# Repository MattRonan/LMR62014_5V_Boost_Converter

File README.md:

# LMR62014_5V_Boost_Converter

A 3.7V to 5V boost converter board using the LMR62014 chip.  Outputs a clean 5V from a 3.7V lipo pack with a compact footprint.  
I designed it as a drop in replacement for a cheap Amazon board that was not only electrically noisey but also emitted an obnoxious audible whine.

Made in Eagle 9.6

Osh Park board: https://oshpark.com/shared_projects/jBZTHgsM

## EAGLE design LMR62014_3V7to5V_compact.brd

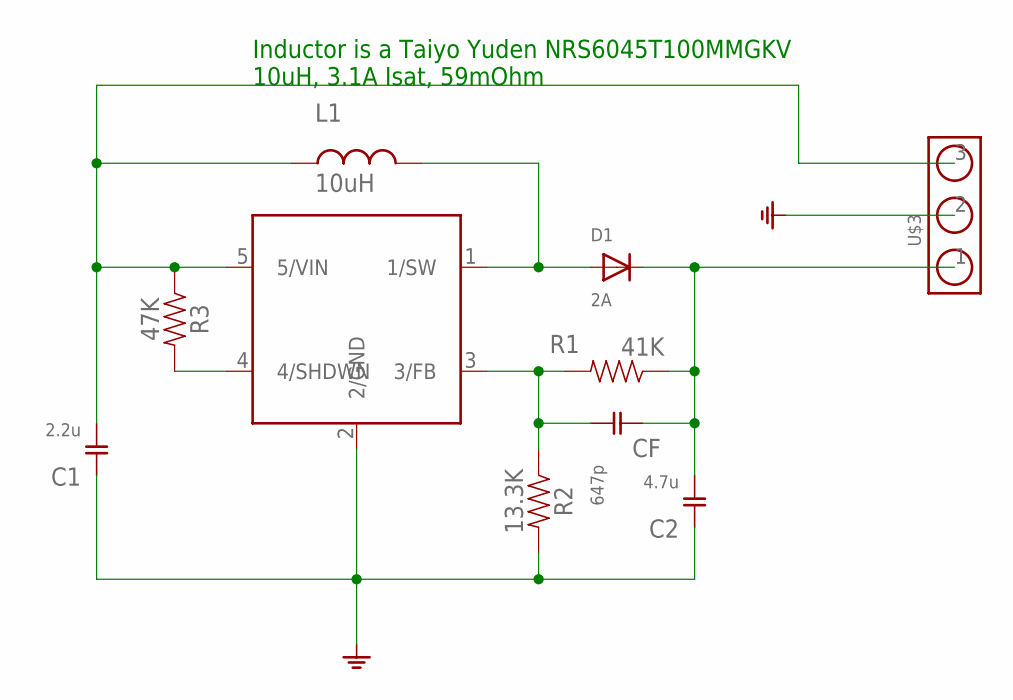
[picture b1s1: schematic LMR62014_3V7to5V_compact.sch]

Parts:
C1: 2.2u; 0603_NORMAL
C2: 4.7u; 0603_NORMAL
CF: 647p; 0603_NORMAL
D1: 2A; SOD-123FL
L1: 10uH; INDUCTOR_SMALL
R1: 41K; 0603_NORMAL
R2: 13.3K; 0603_NORMAL
R3: 47K; 0603_NORMAL
U$1: LMR62014; SOT23-5
U$3: HEADER_1X32.54; 1X3_.1"_2.54MM

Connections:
GND: C1.1, C2.1, R2.2, U$1.2 (2/GND), U$3.2
unnamed: CF.2, R1.2, R2.1, U$1.3 (3/FB)
unnamed: D1.A, L1.P$2 (2), U$1.1 (1/SW)
unnamed: C2.2, CF.1, D1.C, R1.1, U$3.1
unnamed: R3.2, U$1.4 (4/SHDWN)
VIN: C1.2, L1.P$1 (1), R3.1, U$1.5 (5/VIN), U$3.3

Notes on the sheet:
Inductor is a Taiyo Yuden NRS6045T100MMGKV 10uH, 3.1A Isat, 59mOhm

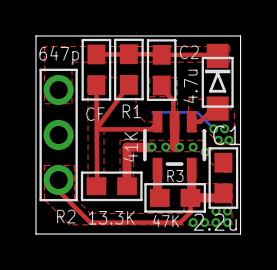
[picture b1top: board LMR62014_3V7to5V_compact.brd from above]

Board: 2 copper layers, 11.4 x 11.0 mm, 10 parts (1 on the bottom side), 6 nets.

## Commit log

2022-08-10 Create BOM
2022-08-10 Create LICENSE
